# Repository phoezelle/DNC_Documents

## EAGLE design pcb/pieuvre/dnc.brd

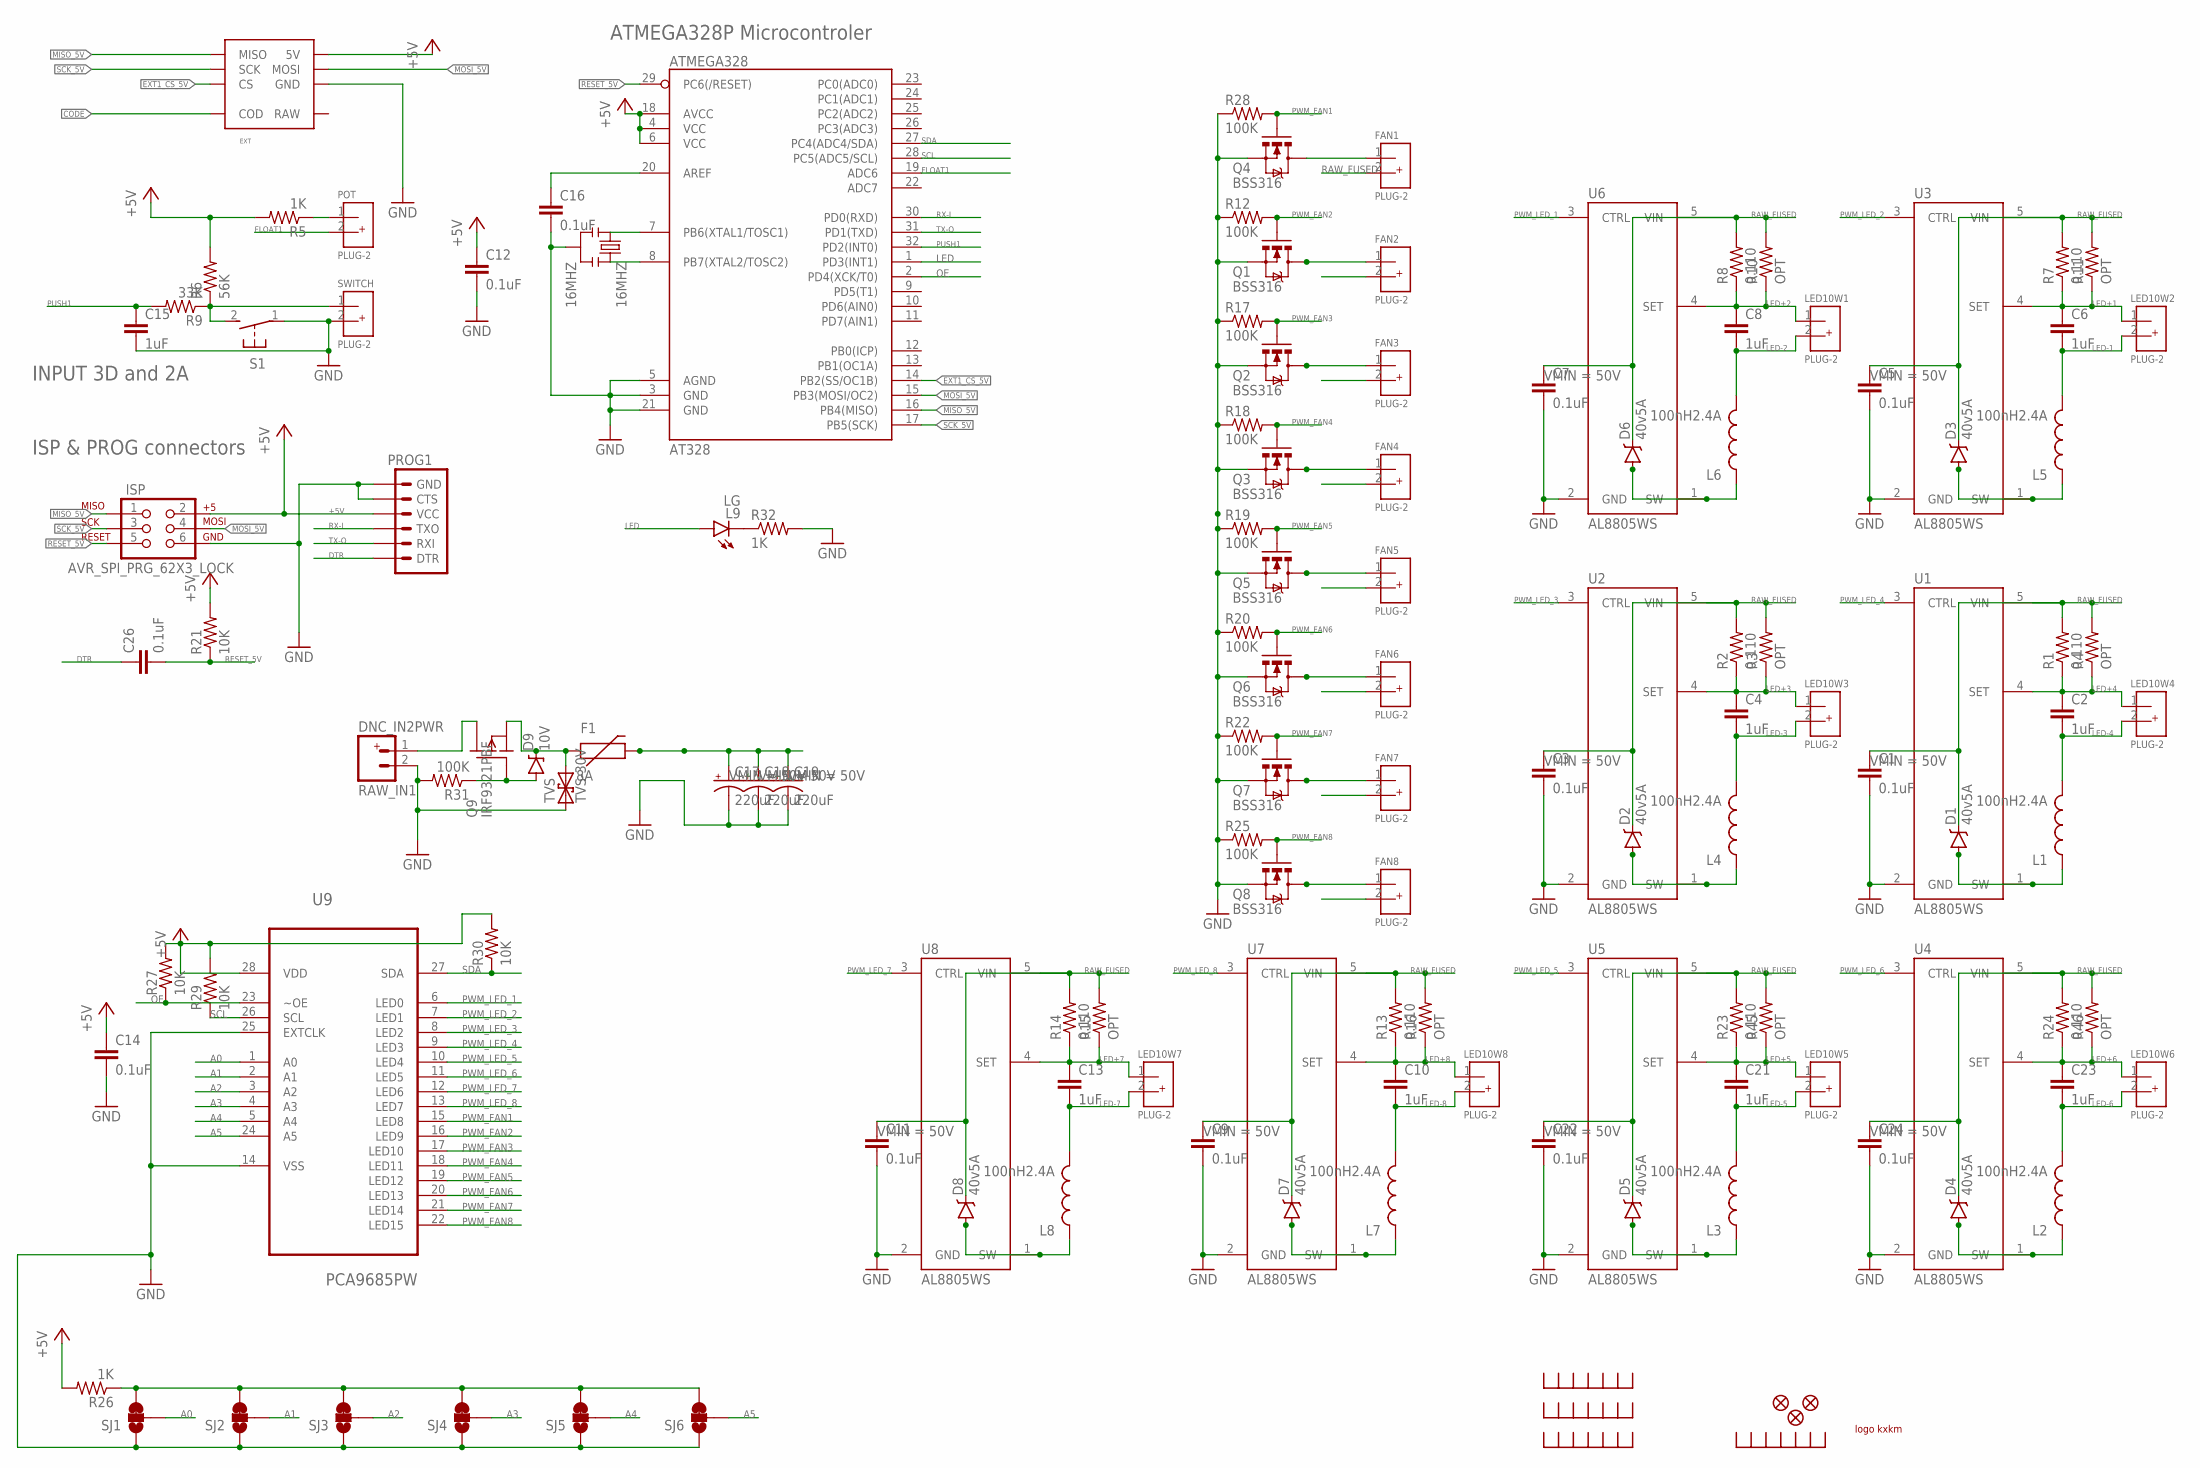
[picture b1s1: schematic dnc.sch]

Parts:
16MHZ: 16MHZ; RESONATOR-SMD
AT328: ATMEGA328; TQFP32-08
C1, C3, C5, C7, C9, C11, C12, C14, C16, C22, C24, C26: 0.1uF; C0603
C2, C4, C6, C8, C10, C13, C15, C21, C23: 1uF; C0603
C17, C18, C19: 220uF; PANASONIC_E
D1, D2, D3, D4, D5, D6, D7, D8: 40v5A; DO-221
D9: 10V; SOD-123
EXT1: EXT; EXTPINDNC
F1: 8A; PTC
FAN1, FAN2, FAN3, FAN4, FAN5, FAN6, FAN7, FAN8: PLUG-2; PLUG_02
ISP: AVR_SPI_PRG_62X3_LOCK; 2X3_LOCK
JP13, JP14, JP19: FIDUCIAL1X2.5; FIDUCIAL-1X2.5
L1, L2, L3, L4, L5, L6, L7, L8: 100nH2.4A; CDRH125
L9: LG; LED-1206
LED10W1, LED10W2, LED10W3, LED10W4, LED10W5, LED10W6, LED10W7, LED10W8: PLUG-2; PLUG_02
POT: PLUG-2; PLUG_02
PROG1: ARDUINO_SERIAL_PROGRAMLOCK; 1X06_LOCK
Q1, Q2, Q3, Q4, Q5, Q6, Q7, Q8: BSS316; SOT23-3
Q9: IRF9321PBF; SO-8
R1, R2, R7, R8, R13, R14, R23, R24: 0.110; R0805
R3, R4, R10, R11, R15, R16, R45, R46: OPT; R0805
R5, R26, R32: 1K; 0603-RES
R6: 56K; 0603-RES
R9: 33K; 0603-RES
R12, R17, R18, R19, R20, R22, R25, R28, R31: 100K; 0603-RES
R21, R27, R29, R30: 10K; 0603-RES
RAW_IN1: DNC_IN2PWR; DNC_IN2_PWR
S1: 31-XX; B3F-31XX
SJ1, SJ2, SJ3, SJ4, SJ5, SJ6: JUMPER-PAD-3-2OF3_NC_BY_TRACE_LARGE; PAD-JUMPER-3-2OF3_NC_BY_TRACE_YES_SILK_LARGE
SWITCH: PLUG-2; PLUG_02
TVS: TVS-30V; SMA-DIODE
U1, U2, U3, U4, U5, U6, U7, U8: AL8805WS; SOT23-5
U9: PCA9685PW; SOP65P640X110-28N
U$1, U$3, U$4, U$5: RADIATEUR; RADIATEUR_577102B00000G
U$2: LOGOSIZE2; KXKMLOGO2

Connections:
+5V: AT328.4 (VCC), AT328.6 (VCC), AT328.18 (AVCC), C12.1, C14.1, EXT1.5V, ISP.2, PROG1.4 (VCC), R5.2, R6.2, R21.2, R26.2, R27.2, R29.2, R30.2, U9.28 (VDD)
A0: SJ1.2, U9.1 (A0)
A1: SJ2.2, U9.2 (A1)
A2: SJ3.2, U9.3 (A2)
A3: SJ4.2, U9.4 (A3)
A4: SJ5.2, U9.5 (A4)
A5: SJ6.2, U9.24 (A5)
AREF: AT328.20 (AREF), C16.1
CODE: EXT1.RETOURANALOG (COD)
DTR: C26.1, PROG1.1 (DTR)
EXT1_CS_5V: AT328.14 (PB2(SS/OC1B)), EXT1./CS (CS)
FLOAT1: AT328.19 (ADC6), POT.2
GND: 16MHZ.2, AT328.3 (GND), AT328.5 (AGND), AT328.21 (GND), C1.2, C3.2, C5.2, C7.2, C9.2, C11.2, C12.2, C14.2, C15.2, C16.2, C17.-, C18.-, C19.-, C22.2, C24.2, EXT1.1_GND (GND), EXT1.GND2 (GND), ISP.6, PROG1.5 (CTS), PROG1.6 (GND), Q1.2 (S), Q2.2 (S), Q3.2 (S), Q4.2 (S), Q5.2 (S), Q6.2 (S), Q7.2 (S), Q8.2 (S), R12.1, R17.1, R18.1, R19.1, R20.1, R22.1, R25.1, R28.1, R31.2, R32.2, RAW_IN1.2 (-), S1.1, SJ1.1, SJ2.1, SJ3.1, SJ4.1, SJ5.1, SJ6.1, SWITCH.2, TVS.A (1), U1.2 (GND), U2.2 (GND), U3.2 (GND), U4.2 (GND), U5.2 (GND), U6.2 (GND), U7.2 (GND), U8.2 (GND), U9.14 (VSS), U9.25 (EXTCLK)
LED: AT328.1 (PD3(INT1)), L9.A
LED+1: C6.1, LED10W2.1, R7.1, R11.1, U3.4 (SET)
LED+2: C8.1, LED10W1.1, R8.1, R10.1, U6.4 (SET)
LED+3: C4.1, LED10W3.1, R2.1, R3.1, U2.4 (SET)
LED+4: C2.1, LED10W4.1, R1.1, R4.1, U1.4 (SET)
LED+5: C21.1, LED10W5.1, R23.1, R45.1, U5.4 (SET)
LED+6: C23.1, LED10W6.1, R24.1, R46.1, U4.4 (SET)
LED+7: C13.1, LED10W7.1, R14.1, R15.1, U8.4 (SET)
LED+8: C10.1, LED10W8.1, R13.1, R16.1, U7.4 (SET)
LED-1: C6.2, L5.2, LED10W2.2
LED-2: C8.2, L6.2, LED10W1.2
LED-3: C4.2, L4.2, LED10W3.2
LED-4: C2.2, L1.2, LED10W4.2
LED-5: C21.2, L3.2, LED10W5.2
LED-6: C23.2, L2.2, LED10W6.2
LED-7: C13.2, L8.2, LED10W7.2
LED-8: C10.2, L7.2, LED10W8.2
MISO_5V: AT328.16 (PB4(MISO)), EXT1.MISO, ISP.1
MOSI_5V: AT328.15 (PB3(MOSI/OC2)), EXT1.MOSI, ISP.4
unnamed: D1.A, L1.1, U1.1 (SW)
unnamed: FAN1.1, Q4.3 (D)
unnamed: D2.A, L4.1, U2.1 (SW)
unnamed: D4.A, L2.1, U4.1 (SW)
unnamed: D5.A, L3.1, U5.1 (SW)
unnamed: D3.A, L5.1, U3.1 (SW)
unnamed: D6.A, L6.1, U6.1 (SW)
unnamed: D7.A, L7.1, U7.1 (SW)
unnamed: D8.A, L8.1, U8.1 (SW)
unnamed: FAN2.1, Q1.3 (D)
unnamed: FAN3.1, Q2.3 (D)
unnamed: FAN4.1, Q3.3 (D)
unnamed: FAN5.1, Q5.3 (D)
unnamed: FAN6.1, Q6.3 (D)
unnamed: FAN7.1, Q7.3 (D)
unnamed: FAN8.1, Q8.3 (D)
unnamed: R6.1, R9.1, S1.2 (S), SWITCH.1
unnamed: POT.1, R5.1
unnamed: R26.1, SJ1.3, SJ2.3, SJ3.3, SJ4.3, SJ5.3, SJ6.3
unnamed: L9.C, R32.1
unnamed: 16MHZ.1, AT328.7 (PB6(XTAL1/TOSC1))
unnamed: 16MHZ.3, AT328.8 (PB7(XTAL2/TOSC2))
OE: AT328.2 (PD4(XCK/T0)), R27.1, U9.23 (~OE)
PROTECT_GATE: D9.A, Q9.4 (G), R31.1
PUSH1: AT328.32 (PD2(INT0)), C15.1, R9.2
PWM_FAN1: Q4.1 (G), R28.2, U9.15 (LED8)
PWM_FAN2: Q1.1 (G), R12.2, U9.16 (LED9)
PWM_FAN3: Q2.1 (G), R17.2, U9.17 (LED10)
PWM_FAN4: Q3.1 (G), R18.2, U9.18 (LED11)
PWM_FAN5: Q5.1 (G), R19.2, U9.19 (LED12)
PWM_FAN6: Q6.1 (G), R20.2, U9.20 (LED13)
PWM_FAN7: Q7.1 (G), R22.2, U9.21 (LED14)
PWM_FAN8: Q8.1 (G), R25.2, U9.22 (LED15)
PWM_LED_1: U6.3 (CTRL), U9.6 (LED0)
PWM_LED_2: U3.3 (CTRL), U9.7 (LED1)
PWM_LED_3: U2.3 (CTRL), U9.8 (LED2)
PWM_LED_4: U1.3 (CTRL), U9.9 (LED3)
PWM_LED_5: U5.3 (CTRL), U9.10 (LED4)
PWM_LED_6: U4.3 (CTRL), U9.11 (LED5)
PWM_LED_7: U8.3 (CTRL), U9.12 (LED6)
PWM_LED_8: U7.3 (CTRL), U9.13 (LED7)
RAW_FUSED: C1.1, C3.1, C5.1, C7.1, C9.1, C11.1, C17.+, C18.+, C19.+, C22.1, C24.1, D1.C, D2.C, D3.C, D4.C, D5.C, D6.C, D7.C, D8.C, F1.P$2 (2), FAN1.2, FAN2.2, FAN3.2, FAN4.2, FAN5.2, FAN6.2, FAN7.2, FAN8.2, R1.2, R2.2, R3.2, R4.2, R7.2, R8.2, R10.2, R11.2, R13.2, R14.2, R15.2, R16.2, R23.2, R24.2, R45.2, R46.2, U1.5 (VIN), U2.5 (VIN), U3.5 (VIN), U4.5 (VIN), U5.5 (VIN), U6.5 (VIN), U7.5 (VIN), U8.5 (VIN)
RAW_POL_PROTECTED1: D9.C, F1.P$1MOV (1), Q9.1 (S), Q9.2 (S), Q9.3 (S), TVS.C (2)
RAW_UNPROTECTED1: Q9.5 (D), Q9.6 (D), Q9.7 (D), Q9.8 (D), RAW_IN1.1 (+)
RESET_5V: AT328.29 (PC6(/RESET)), C26.2, ISP.5, R21.1
RX-I: AT328.30 (PD0(RXD)), PROG1.3 (TXO)
SCK_5V: AT328.17 (PB5(SCK)), EXT1.SCK, ISP.3
SCL: AT328.28 (PC5(ADC5/SCL)), R29.1, U9.26 (SCL)
SDA: AT328.27 (PC4(ADC4/SDA)), R30.1, U9.27 (SDA)
TX-O: AT328.31 (PD1(TXD)), PROG1.2 (RXI)

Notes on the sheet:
ATMEGA328P Microcontroler
ISP & PROG connectors
INPUT 3D and 2A

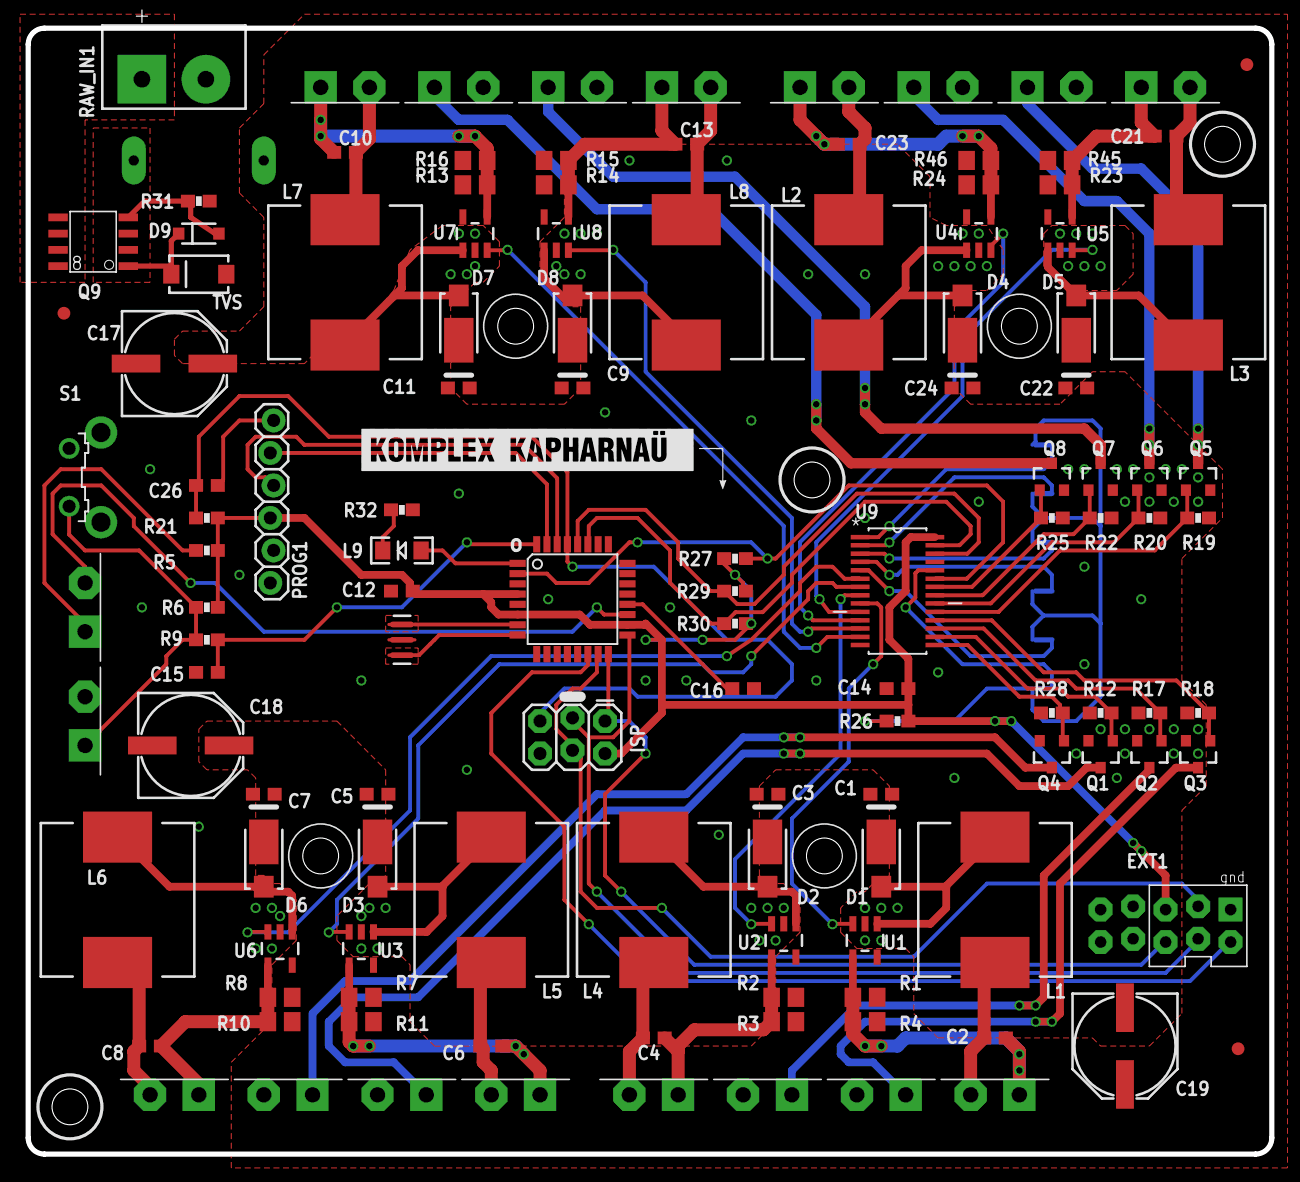
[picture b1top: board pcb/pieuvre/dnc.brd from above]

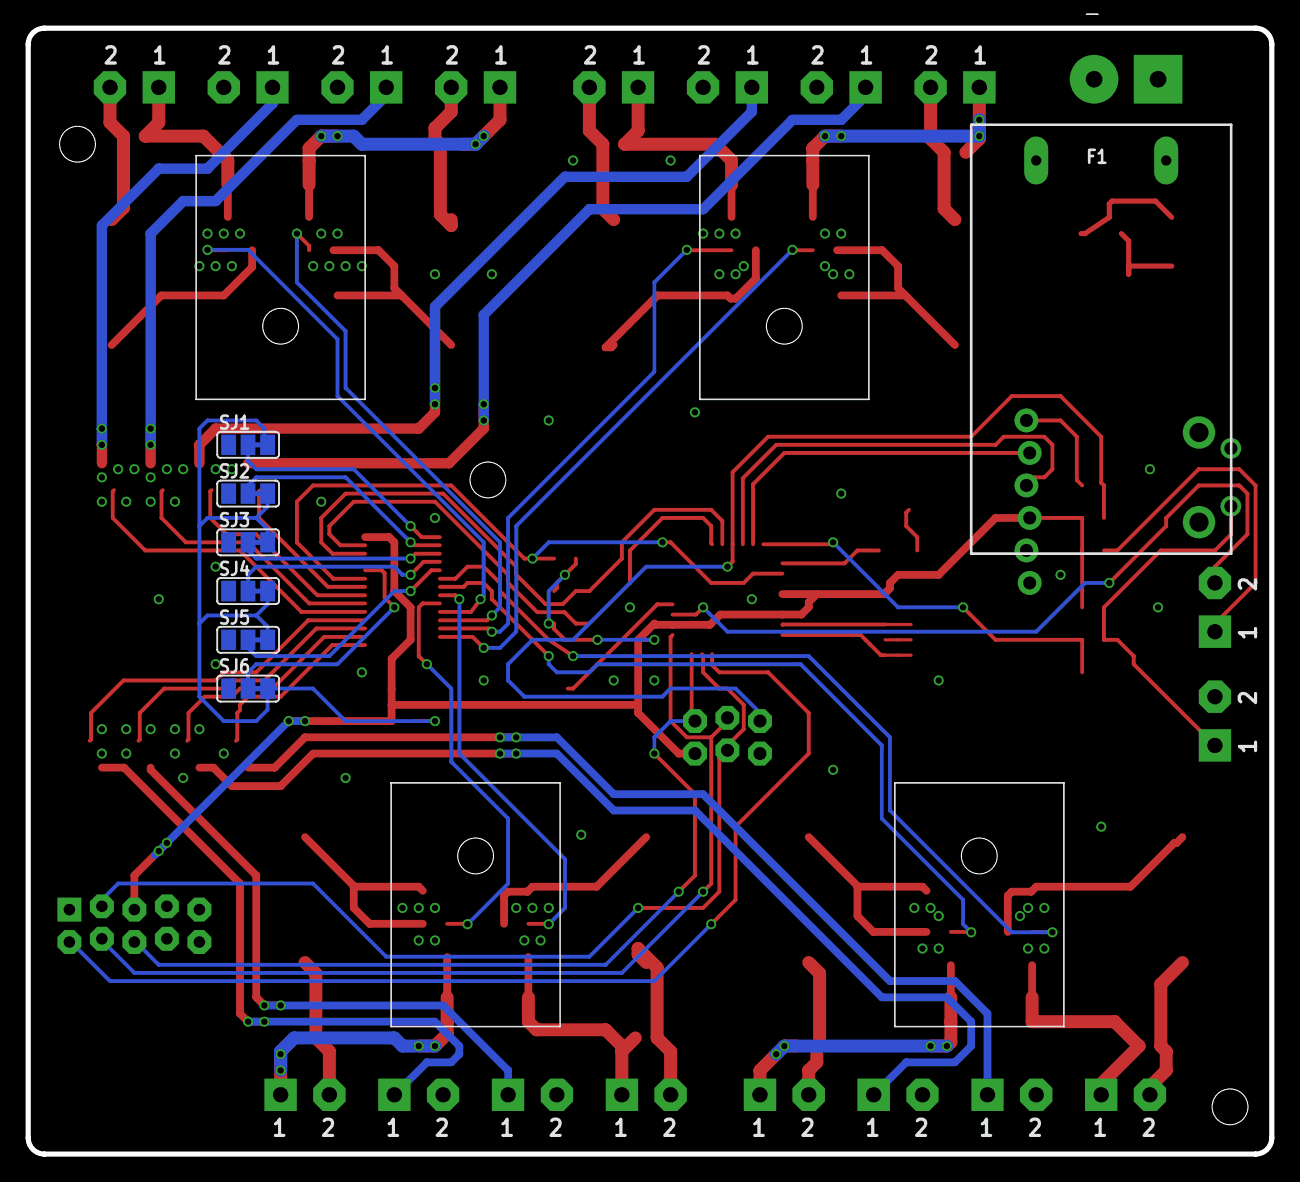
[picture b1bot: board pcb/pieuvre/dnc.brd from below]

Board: 2 copper layers, 97.2 x 88.0 mm, 135 parts (11 on the bottom side), 81 nets.

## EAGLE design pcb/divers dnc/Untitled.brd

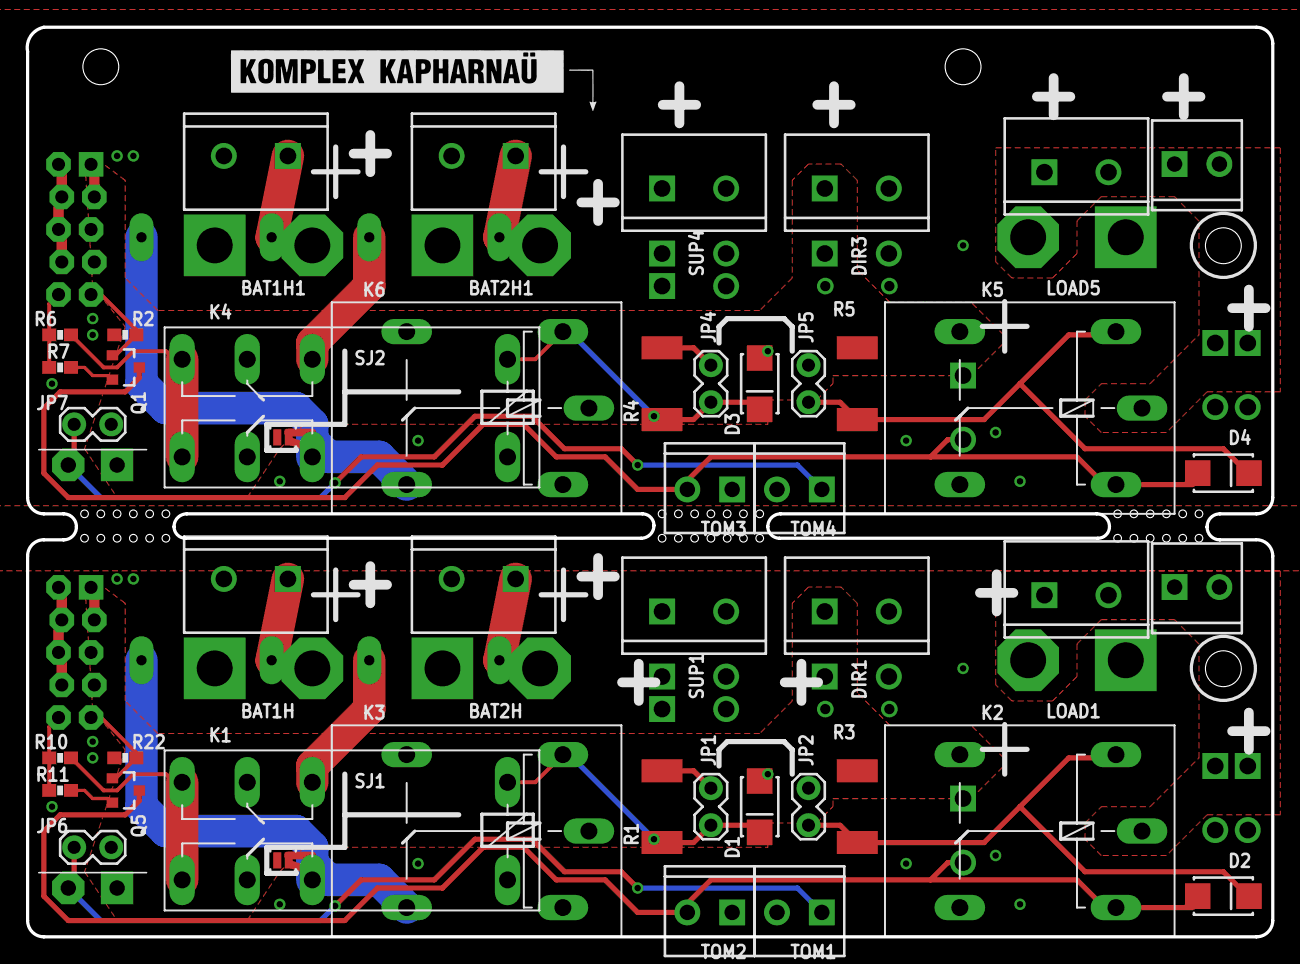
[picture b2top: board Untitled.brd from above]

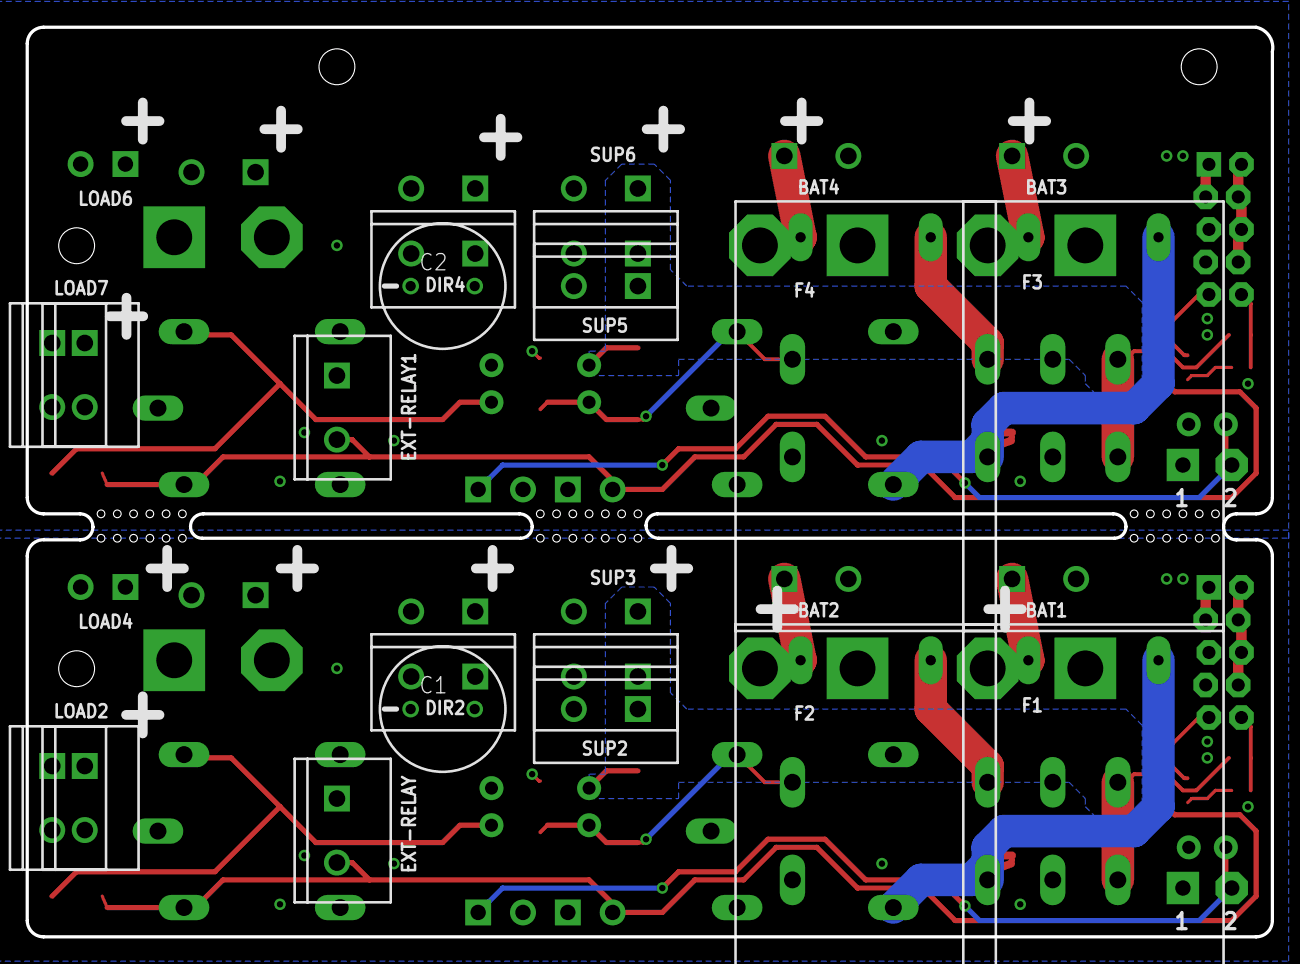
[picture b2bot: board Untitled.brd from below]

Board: 2 copper layers, 97.2 x 71.0 mm, 75 parts (18 on the bottom side), 28 nets.

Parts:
BAT1, BAT2, BAT3, BAT4: M025MM; SCREWTERMINAL-5MM-2
BAT1H, BAT1H1, BAT2H, BAT2H1: M02HOLE; 2X1_HOLE_BIG
C1, C2: SANYO-OSCON_9F
D1, D2, D3, D4: SMA-DIODE_ALT
DIR1, DIR2, DIR3, DIR4: M025MM; SCREWTERMINAL-5MM-2
E$1: KXKMLOGO2
EXT-RELAY, EXT-RELAY1: M025MM; SCREWTERMINAL-5MM-2
F1, F2, F3, F4: 8A; PTC
INTER, INTER1: M02PLUG; PLUG_02
JP1, JP2, JP4, JP5: 24/12; 1X02_LOCK
JP3, JP8: CHARGEUR; 2X5_LOCK
JP6, JP7: ON; 1X02_LOCK
K1, K4: 4052; F4052
K2, K3, K5, K6: G5L; G5LE
LOAD1, LOAD2, LOAD3, LOAD5, LOAD7, LOAD8: M025MM; SCREWTERMINAL-5MM-2
LOAD4, LOAD6: M023.5MM; SCREWTERMINAL-3.5MM-2
PLUG_3.81_2_1, PLUG_3.81_2_3: M02HOLE; 2X1_HOLE_BIG
Q1, Q5: BSS138; SOT23-3
R1, R3, R4, R5: 390; R2512
R2, R6, R10, R22: 100K; 0603-RES
R7, R11: 10K; 0603-RES
SJ1, SJ2: ONLY BATT; SJ_2S-NO
SUP1, SUP2, SUP3, SUP4, SUP5, SUP6: M025MM; SCREWTERMINAL-5MM-2
TOM1, TOM2, TOM3, TOM4: M023.5MM; SCREWTERMINAL-3.5MM-2

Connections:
+TOM: INTER.2, JP6.1, TOM1.1
+TOM1: INTER1.2, JP7.1, TOM4.1
BATT1: F1.P$1MOV, K1.O2, K3.O, SJ1.2
BATT2: F2.P$1MOV, K1.O1
BATT3: F3.P$1MOV, K4.O2, K6.O, SJ2.2
BATT4: F4.P$1MOV, K4.O1
CHARGING: JP3.2, R10.1, R11.2
CHARGING1: JP8.2, R6.1, R7.2
GND: BAT1.2, BAT1H._, BAT2.2, BAT2H._, C1.-, D1.A, DIR1.2, DIR2.2, JP3.4, JP3.6, JP3.8, JP3.10, K1.1, K3.2, LOAD1.2, LOAD2.2, LOAD3.2, LOAD4.2, PLUG_3.81_2_3._, Q5.2, R11.1, R22.1, SUP1.2, SUP2.2, SUP3.2, TOM1.2
GND1: BAT1H1._, BAT2H1._, BAT3.2, BAT4.2, C2.-, D3.A, DIR3.2, DIR4.2, JP8.4, JP8.6, JP8.8, JP8.10, K4.1, K6.2, LOAD5.2, LOAD6.2, LOAD7.2, LOAD8.2, PLUG_3.81_2_1._, Q1.2, R2.1, R7.1, SUP4.2, SUP5.2, SUP6.2, TOM4.2
LOAD: K2.P, LOAD1.1, LOAD2.1, LOAD3.1, LOAD4.1, PLUG_3.81_2_3.+
LOAD1: K5.P, LOAD5.1, LOAD6.1, LOAD7.1, LOAD8.1, PLUG_3.81_2_1.+
unnamed: D1.C, JP1.2, K1.2, K3.1, R1.1
unnamed: BAT1.1, BAT1H.+, F1.P$2
unnamed: BAT2.1, BAT2H.+, F2.P$2
unnamed: D2.C, JP2.2, K2.1, R3.1
unnamed: D3.C, JP4.2, K4.2, K6.1, R4.1
unnamed: D4.C, JP5.2, K5.1, R5.1
unnamed: BAT1H1.+, BAT3.1, F3.P$2
unnamed: BAT2H1.+, BAT4.1, F4.P$2
RELAY_CHARGE_BOARD: JP3.1, Q5.1, R22.2
RELAY_CHARGE_BOARD1: JP8.1, Q1.1, R2.2
SINK_FROM_TOM: D2.A, EXT-RELAY.2, K2.2, Q5.3, TOM2.2
SINK_FROM_TOM1: D4.A, EXT-RELAY1.2, K5.2, Q1.3, TOM3.2
SUPPLY: JP1.1, K1.S1, K1.S2, K3.S, R1.2, R10.2, SUP1.1, SUP2.1, SUP3.1
SUPPLY1: JP4.1, K4.S1, K4.S2, K6.S, R4.2, R6.2, SUP4.1, SUP5.1, SUP6.1
SUPPLY/BATT: C1.+, DIR1.1, DIR2.1, EXT-RELAY.1, INTER.1, JP2.1, JP3.3, JP3.5, JP3.7, JP3.9, JP6.2, K1.P1, K1.P2, K2.S, K3.P, R3.2, SJ1.1
SUPPLY/BATT1: C2.+, DIR3.1, DIR4.1, EXT-RELAY1.1, INTER1.1, JP5.1, JP7.2, JP8.3, JP8.5, JP8.7, JP8.9, K4.P1, K4.P2, K5.S, K6.P, R5.2, SJ2.1

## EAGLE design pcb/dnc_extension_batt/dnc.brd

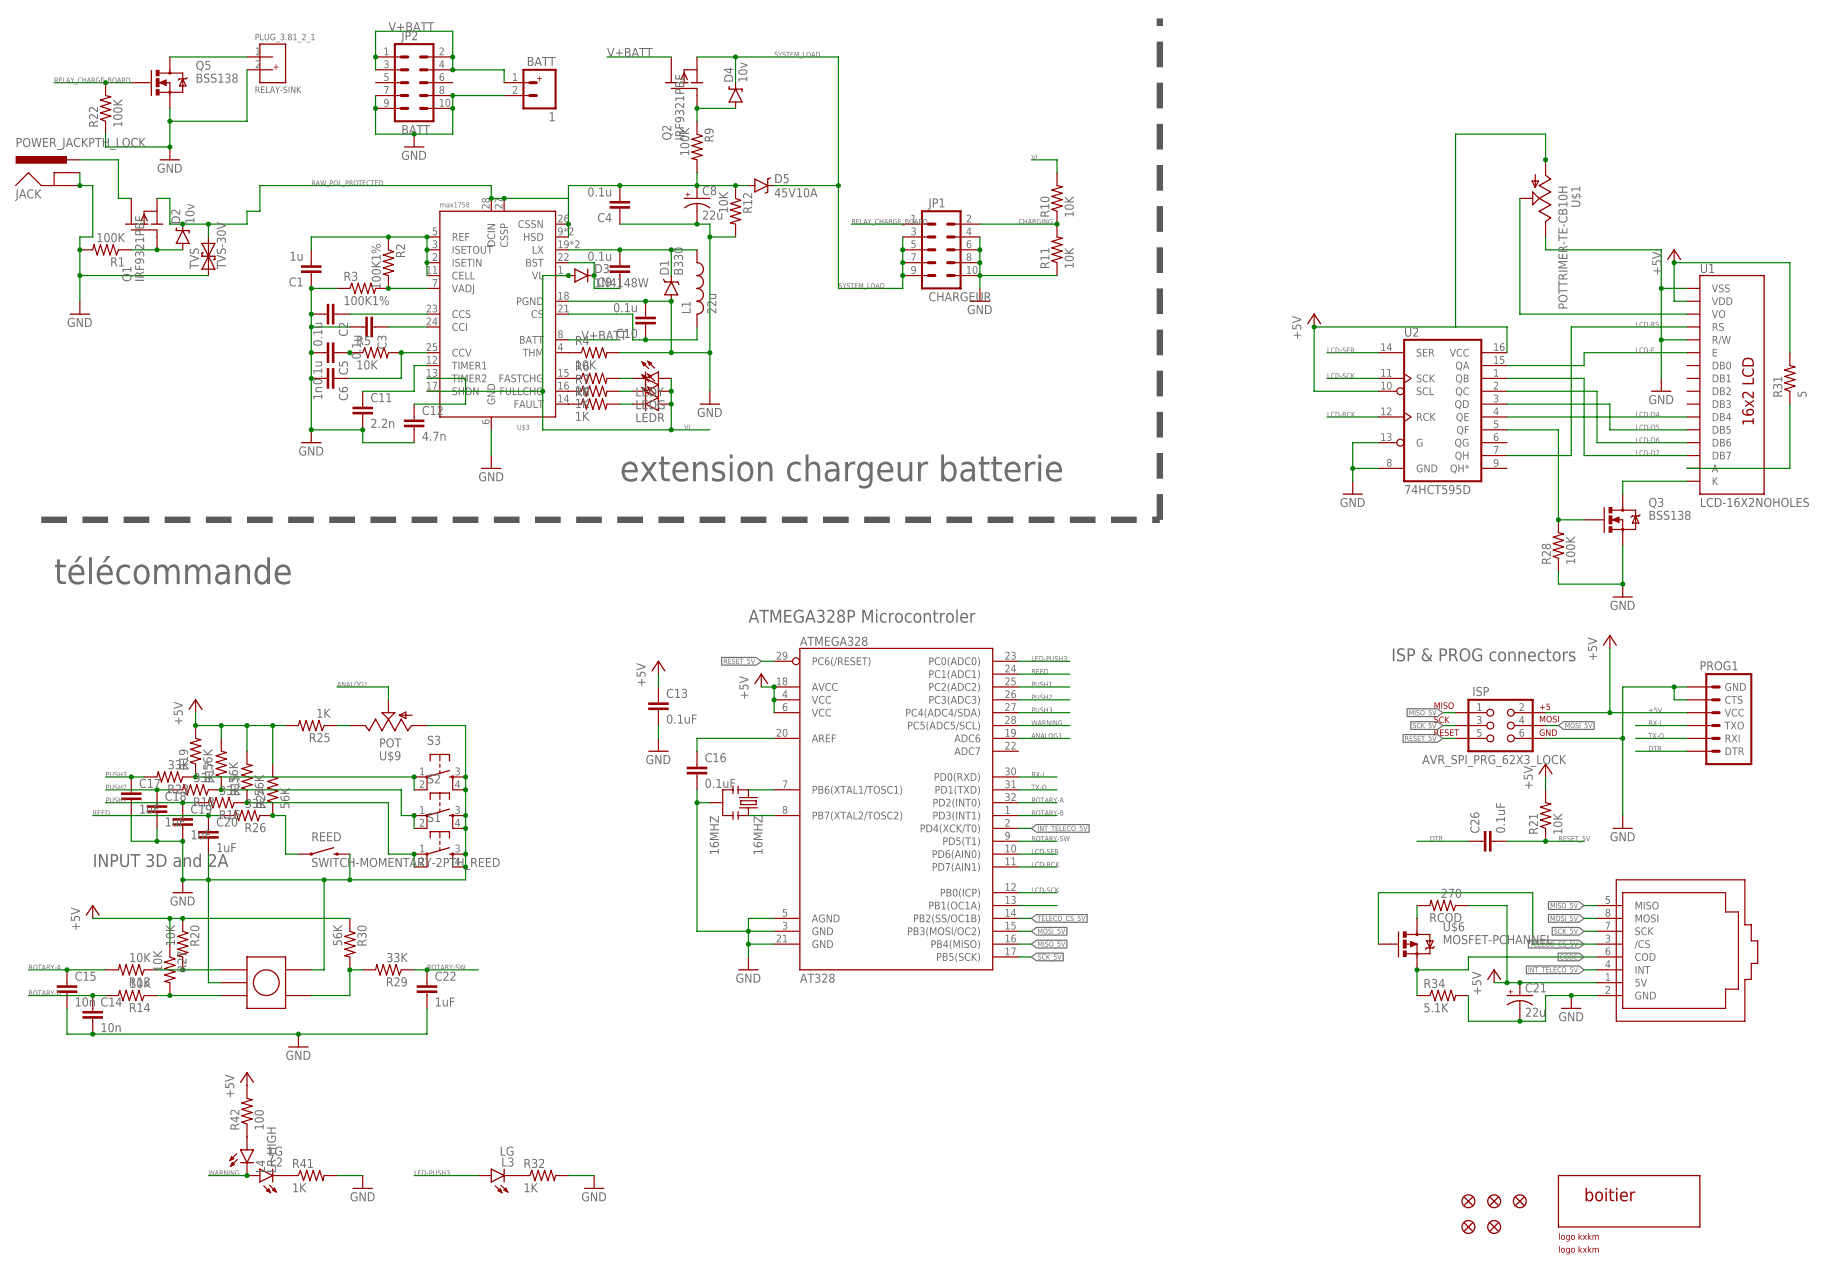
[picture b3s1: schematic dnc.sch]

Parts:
1: BATT; DNC_IN2_PWR
16MHZ: 16MHZ; RESONATOR-SMD
AT328: ATMEGA328; TQFP32-08
C1: 1u; 0603-CAP
C2, C3, C4, C5, C9, C10: 0.1u; 0603-CAP
C6: 1n; 0603-CAP
C8: 22u; PANASONIC_C
C11: 2.2n; 0603-CAP
C12: 4.7n; 0603-CAP
C13, C16, C26: 0.1uF; C0603
C14, C15: 10n; C0603
C17, C18, C19, C20, C22: 1uF; C0603
C21: 22u; EIA3216
D1: B330; SMA-DIODE
D2, D4: 10v; SOD-123
D3: 1N4148W; SOD-123
D5: 45V10A; DPAK
ISP: AVR_SPI_PRG_62X3_LOCK; 2X3_LOCK
JACK: POWER_JACKPTH_LOCK; POWER_JACK_PTH_LOCK
JP1: CHARGEUR; 2X5_LOCK
JP2: BATT; 2X5-RA
JP3, JP4, JP13, JP14, JP19: FIDUCIAL1X2.5; FIDUCIAL-1X2.5
L1: 22u; SRN1060
L2, L3: LG; LED-1206
L4: LR-HIGH; LED-1206
LEDG: LED1206; LED-1206
LEDR: LED1206; LED-1206
LEDY: LED1206; LED-1206
PLUG_3.81_2_1: RELAY-SINK; PLUG_02
PROG1: ARDUINO_SERIAL_PROGRAMLOCK; 1X06_LOCK
Q1, Q2: IRF9321PBF; SO-8
Q3, Q5: BSS138; SOT23-3
R1, R9, R22, R28: 100K; 0603-RES
R2, R3: 100K1%; 0603-RES
R4, R5, R10, R11, R12, R13, R14, R20, R21, R27: 10K; 0603-RES
R6, R7, R8, R25, R32, R41: 1K; 0603-RES
R15, R17, R19, R24, R30: 56K; 0603-RES
R16, R18, R23, R26, R29: 33K; 0603-RES
R31: 5; 0805
R34: 5.1K; 0603-RES
R42: 100; 0603-RES
RCOD: 270; 0603-RES
REED: SWITCH-MOMENTARY-2PTH_REED; REED_SWITCH_PTH
S1, S2, S3: TAC_SWITCHPTH; TACTILE-PTH
TVS: TVS-30V; SMA-DIODE
U1: LCD-16X2NOHOLES; LCD-16X2_NOHOLES
U2: 74HCT595D; SO16
U$1: POTTRIMER-TE-CB10H; TRIMER-TE
U$2, U$6MOV: LOGOSIZE2; KXKMLOGO2
U$3: MAX1758; SSOP28
U$5: BOITIERBOITIER_FARNELLE_479-0020-0; BOX_SIZE
U$6: MOSFET-PCHANNEL; SOT23-3
U$7: ROTARYEC12D1564404; ROTARY_ALPS_EC12
U$8: RJ45-EXTDNC; RJ45-TRAFO
U$9: POT; POT_ALPS

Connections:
+5V: AT328.4 (VCC), AT328.6 (VCC), AT328.18 (AVCC), C13.1, C21.A (+), ISP.2, PROG1.4 (VCC), R15.2, R17.2, R19.2, R20.1, R21.2, R24.2, R25.2, R27.1, R30.1, R31.2, R42.2, RCOD.1, U1.2 (VDD), U2.10 (SCL), U2.16 (VCC), U$1.1 (A), U$8.1 (5V)
ANALOG1: AT328.19 (ADC6), U$9.2 (S)
AREF: AT328.20 (AREF), C16.1
CHARGING: JP1.2, R10.1, R11.2
CODE: R34.1, U$6.2 (S), U$8.6 (COD)
DTR: C26.1, PROG1.1 (DTR)
GND: 1.2 (-), 16MHZ.2, AT328.3 (GND), AT328.5 (AGND), AT328.21 (GND), C1.1, C2.2, C3.2, C4.1, C5.2, C6.2, C8.-, C10.2, C11.2, C12.2, C13.2, C14.2, C15.2, C16.2, C17.2, C18.2, C19.2, C20.2, C21.C (-), C22.2, D1.A, ISP.6, JACK.GND, JACK.GNDBREAK, JP1.4, JP1.6, JP1.8, JP1.10, JP2.7, JP2.8, JP2.9, JP2.10, PLUG_3.81_2_1.2, PROG1.5 (CTS), PROG1.6 (GND), Q3.2 (S), Q5.2 (S), R1.2, R3.1, R4.2, R11.1, R12.2, R22.1, R28.1, R32.2, R34.2, R41.2, REED.P$2 (2), S1.3, S1.4, S2.3, S2.4, S3.3, S3.4, TVS.A (1), U1.1 (VSS), U1.5 (R/W), U2.8 (GND), U2.13 (G), U$1.3 (E), U$3.6 (GND), U$3.18 (PGND), U$7.C (COM), U$7.D (SW1), U$8.2 (GND), U$9.1 (A)
INT_TELECO_5V: AT328.2 (PD4(XCK/T0)), U$8.4 (INT)
LCD-D4: U1.11 (DB4), U2.4 (QE)
LCD-D5: U1.12 (DB5), U2.3 (QD)
LCD-D6: U1.13 (DB6), U2.2 (QC)
LCD-D7: U1.14 (DB7), U2.1 (QB)
LCD-E: U1.6 (E), U2.15 (QA)
LCD-LED-CONTROL: Q3.1 (G), R28.2, U2.5 (QF)
LCD-RCK: AT328.11 (PD7(AIN1)), U2.12 (RCK)
LCD-RS: U1.4 (RS), U2.7 (QH)
LCD-SCK: AT328.12 (PB0(ICP)), U2.11 (SCK)
LCD-SER: AT328.10 (PD6(AIN0)), U2.14 (SER)
LED-PUSH3: AT328.23 (PC0(ADC0)), L3.A
MISO_5V: AT328.16 (PB4(MISO)), ISP.1, U$8.5 (MISO)
MOSI_5V: AT328.15 (PB3(MOSI/OC2)), ISP.4, U$8.8 (MOSI)
unnamed: C1.2, R2.1, U$3.2 (ISETIN), U$3.3 (ISETOUT), U$3.5 (REF), U$3.11 (CELL)
unnamed: C9.2, D1.C, L1.P$1 (1), U$3.19 (LX), U$3.20 (LX)
unnamed: R2.2, R3.2, U$3.7 (VADJ)
unnamed: R4.1, U$3.4 (THM)
unnamed: C5.1, R5.1
unnamed: C2.1, U$3.23 (CCS)
unnamed: C3.1, U$3.24 (CCI)
unnamed: C6.1, R5.2, U$3.25 (CCV)
unnamed: R6.1, U$3.15 (FASTCHG)
unnamed: R7.1, U$3.16 (FULLCHG)
unnamed: R8.1, U$3.14 (FAULT)
unnamed: LEDY.C, R6.2
unnamed: LEDG.C, R7.2
unnamed: LEDR.C, R8.2
unnamed: C11.1, U$3.12 (TIMER1)
unnamed: C9.1, D3.C, U$3.22 (BST)
unnamed: C10.1, L1.P$2 (2), U$3.21 (CS)
unnamed: PLUG_3.81_2_1.1, Q5.3 (D)
unnamed: D4.A, Q2.4 (G), R9.1
unnamed: C12.1, U$3.13 (TIMER2)
unnamed: R15.1, R16.1, S1.1, S1.2
unnamed: R14.1, R27.2, U$7.A
unnamed: R17.1, R18.1, S2.1, S2.2
unnamed: R13.1, R20.2, U$7.B
unnamed: R19.1, R23.1, S3.1, S3.2
unnamed: R25.1, U$9.3 (E)
unnamed: R24.1, R26.1, REED.P$1 (1)
unnamed: L4.A, R42.1
unnamed: L2.C, R41.1
unnamed: R29.2, R30.2, U$7.E (SW2)
unnamed: R31.1, U1.15 (A)
unnamed: U1.3 (VO), U$1.2 (S)
unnamed: Q3.3 (D), U1.16 (K)
unnamed: L3.C, R32.1
unnamed: RCOD.2, U$6.3 (D)
unnamed: 16MHZ.1, AT328.7 (PB6(XTAL1/TOSC1))
unnamed: 16MHZ.3, AT328.8 (PB7(XTAL2/TOSC2))
PROTECT_GATE: D2.A, Q1.4 (G), R1.1
PUSH1: AT328.25 (PC2(ADC2)), C19.1, R16.2
PUSH2: AT328.26 (PC3(ADC3)), C18.1, R18.2
PUSH3: AT328.27 (PC4(ADC4/SDA)), C17.1, R23.2
RAW_POL_PROTECTED: C4.2, C8.+, D2.C, D5.1 (A), D5.3 (A), Q1.1 (S), Q1.2 (S), Q1.3 (S), R9.2, R12.1, TVS.C (2), U$3.9 (HSD), U$3.10 (HSD), U$3.26 (CSSN), U$3.27 (CSSP), U$3.28 (DCIN)
RAW_UNPROTECTED1: JACK.PWR, Q1.5 (D), Q1.6 (D), Q1.7 (D), Q1.8 (D)
REED: AT328.24 (PC1(ADC1)), C20.1, R26.2
RELAY_CHARGE_BOARD: JP1.1, Q5.1 (G), R22.2
RESET_5V: AT328.29 (PC6(/RESET)), C26.2, ISP.5, R21.1
ROTARY-A: AT328.32 (PD2(INT0)), C15.1, R13.2
ROTARY-B: AT328.1 (PD3(INT1)), C14.1, R14.2
ROTARY-SW: AT328.9 (PD5(T1)), C22.1, R29.1
RX-I: AT328.30 (PD0(RXD)), PROG1.3 (TXO)
SCK_5V: AT328.17 (PB5(SCK)), ISP.3, U$8.7 (SCK)
SYSTEM_LOAD: D4.C, D5.4 (C), JP1.3, JP1.5, JP1.7, JP1.9, Q2.1 (S), Q2.2 (S), Q2.3 (S)
TELECO_CS_5V: AT328.14 (PB2(SS/OC1B)), U$6.1 (G), U$8.3 (/CS)
TX-O: AT328.31 (PD1(TXD)), PROG1.2 (RXI)
V+BATT: 1.1 (+), JP2.1, JP2.2, JP2.3, JP2.4, Q2.5 (D), Q2.6 (D), Q2.7 (D), Q2.8 (D), U$3.8 (BATT)
VL: D3.A, LEDG.A, LEDR.A, LEDY.A, R10.2, U$3.1 (VL), U$3.17 (SHDN)
WARNING: AT328.28 (PC5(ADC5/SCL)), L2.A, L4.C

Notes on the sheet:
extension chargeur batterie
télécommande
ATMEGA328P Microcontroler
ISP & PROG connectors
INPUT 3D and 2A

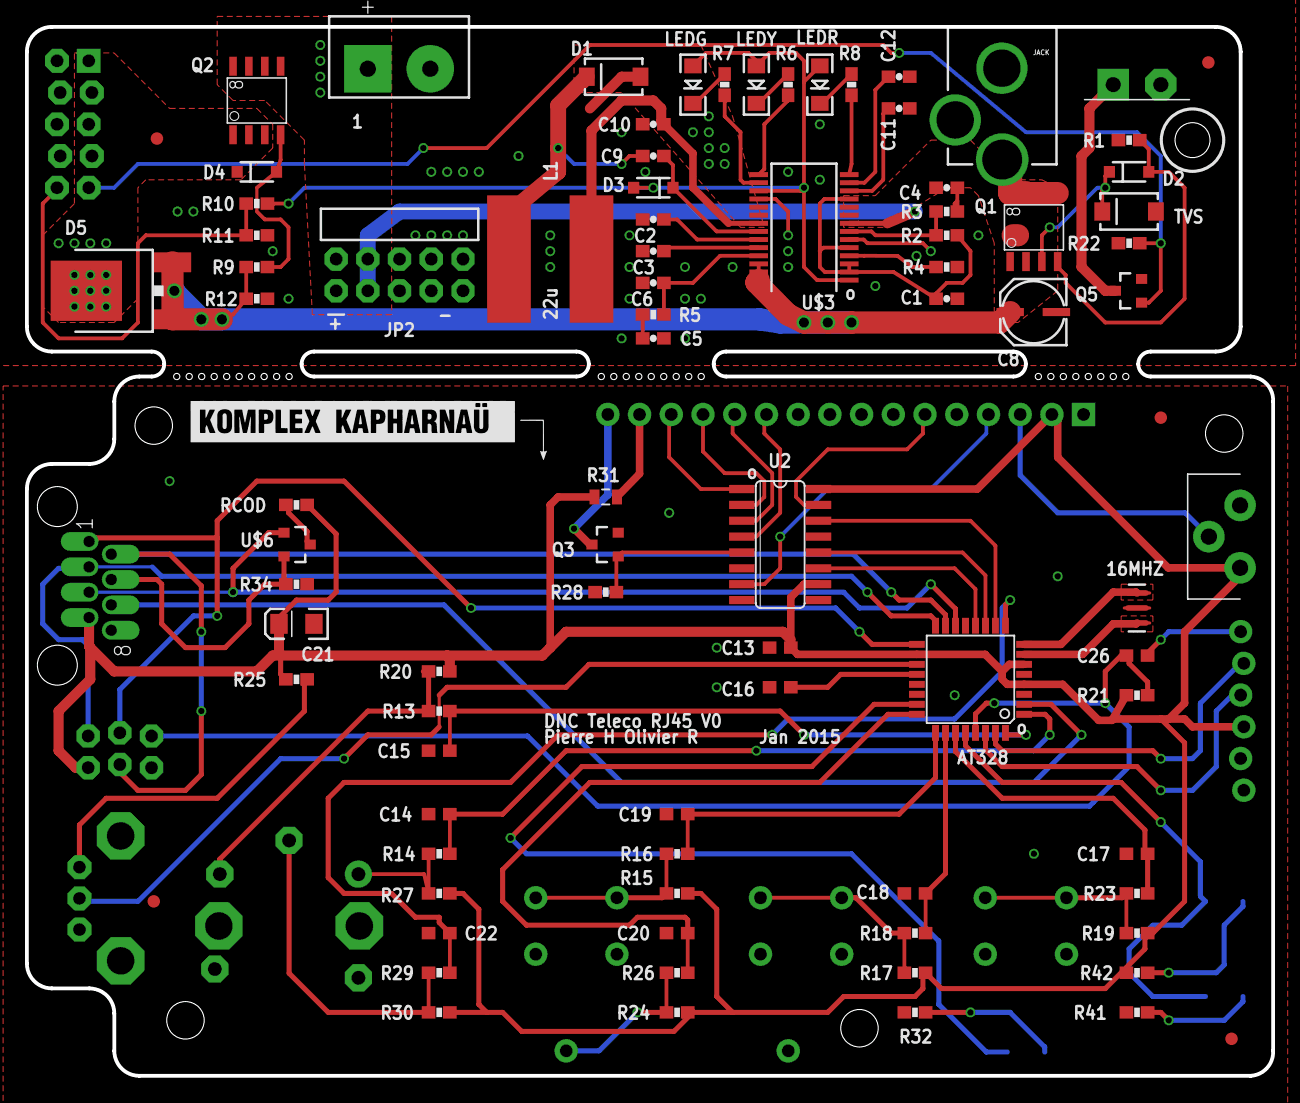
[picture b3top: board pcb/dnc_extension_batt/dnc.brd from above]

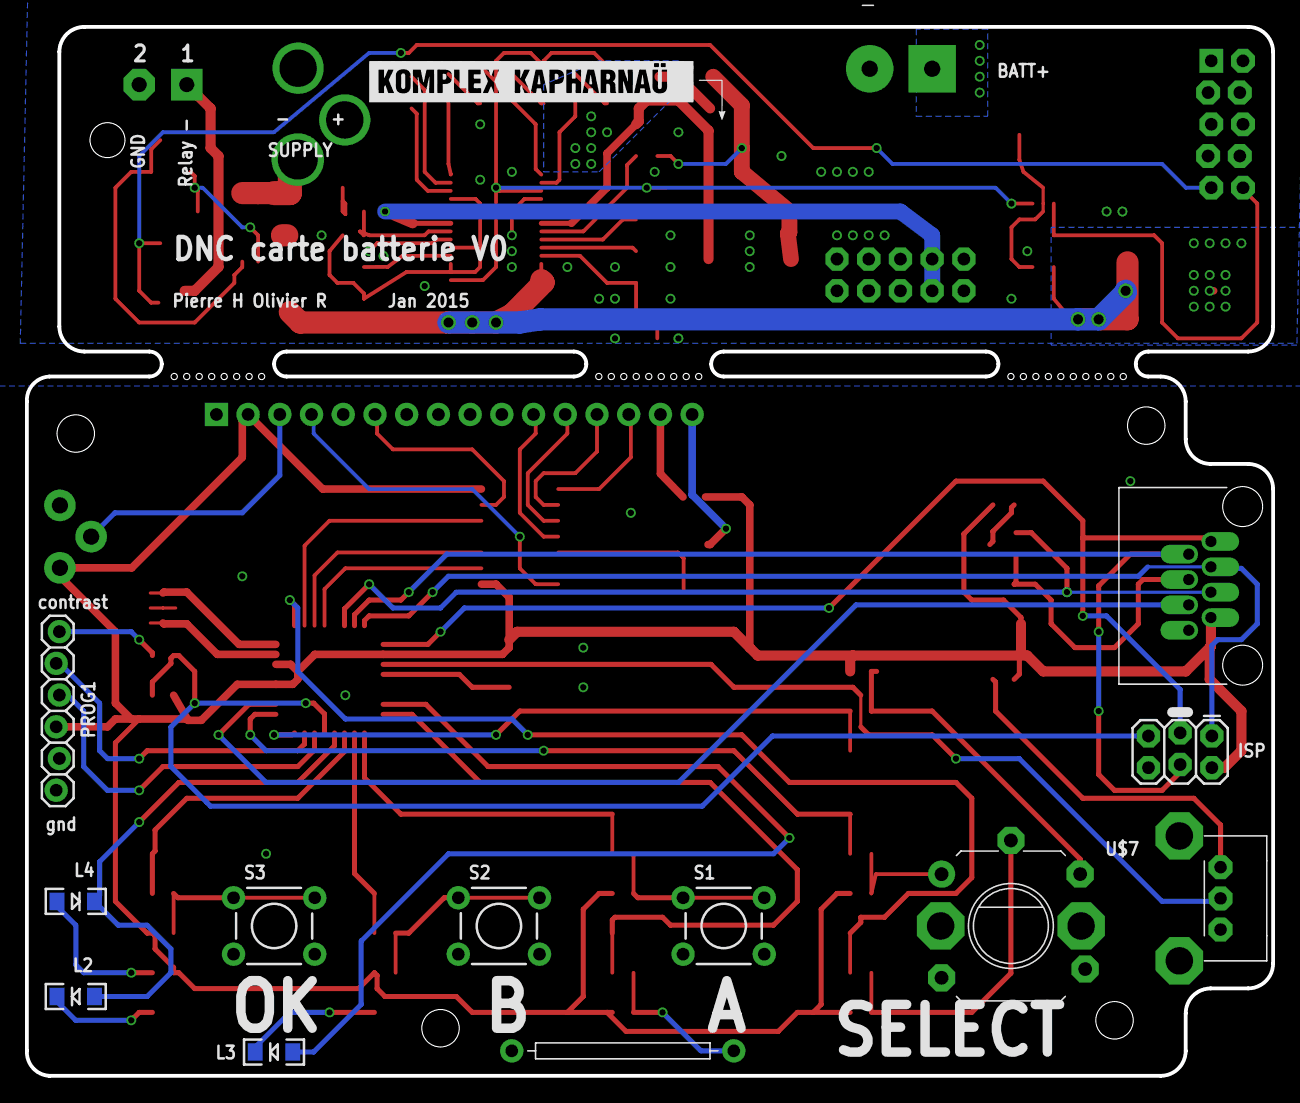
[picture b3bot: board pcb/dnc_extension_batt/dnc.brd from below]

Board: 2 copper layers, 99.8 x 84.0 mm, 104 parts (14 on the bottom side), 78 nets.

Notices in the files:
parts and their libraries:
SparkFun-DiscreteSemi: Licensing: Creative Commons ShareAlike 4.0 International - https://creativecommons.org/licenses/by-sa/4.0
SparkFun: Licensing: CC v3.0 Share-Alike You are welcome to use this library for commercial purposes.
